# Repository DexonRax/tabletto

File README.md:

# Tabletto V1S

> A ridiculously fast DIY osu! "tablet" built around a **SCARA arm** mechanism, powered by an **RP2040** (RP2040-Zero) and **dual AS5600 magnetic rotary encoders**.

Tabletto V1S was designed with one goal in mind: **the lowest possible input latency** using inexpensive, easy-to-source components, fully 3D printed mechanics, and custom open-source PCBs.

---

# Gallery

---

# Features

* ⚡ **1000 Hz report rate** (1 ms USB HID polling)
* 🎯 Minimal cursor jitter
* 🚀 Faster than most commercial graphics tablets
* 🖨️ Fully 3D printable mechanical design
* 🔩 Custom open-source **KiCad PCBs** (base + arm sensor board)
* 🧠 On-device forward kinematics — standalone, works with **OpenTabletDriver**
* 🔘 Physical button: **short press** toggles the tablet, **hold 3 s** to calibrate
* 💾 Calibration stored in the RP2040's flash, survives power cycles

---

# How it works

Tabletto uses a **SCARA (Selective Compliance Assembly Robot Arm)** mechanism.

Two **AS5600 magnetic rotary encoders** measure the angle of each arm joint — one lives on the base PCB, the other on a small board at the elbow. The RP2040 firmware reads both encoders over two separate I2C buses and computes the pen position with forward kinematics, then sends it to the host as a vendor-defined HID report.

Because the sensors provide high-resolution angle measurements and the mechanism has very little moving mass, the result is an extremely responsive pointing device well suited for rhythm games like osu!.

---

# Hardware

Required components:

| Quantity | Part                            |
| -------- | ------------------------------- |
| 1        | RP2040-Zero (or similar module) |
| 2        | AS5600 Magnetic Rotary Encoder  |
| 2        | MR128ZZ 8x12x3.5mm Bearings     |
| 4        | 4.7kΩ Resistor                  |
| 1        | 100nF Capacitor                 |
| 1        | JST XH 2.54mm straight connector|
| 1        | JST XH 2.54mm male cable        |
| 1        | Keyboard Switch                 |
| 4        | 10mm M3 Screws                  |
| 2        | 4x3mm Diametral magnets         |
| —        | 3D Printed Parts                |
| —        | PCBs - from `V1S/pcb`           |

Both boards have **3.2 mm M3 mounting holes**.

---

# PCBs

The electronic design is open source and lives in [V1S/pcb](V1S/pcb):

* **`pcb/base`** — base board: RP2040-Zero module, one AS5600, 4.7kΩ I2C pull-ups, calibration button, and a 4-pin connector to the arm board.
* **`pcb/arm`** — elbow board: the second AS5600 with a 100 nF decoupling cap, connected over a short 4-pin cable.

Open the `.kicad_sch` / `.kicad_pcb` files in KiCad 8+ and order them from any PCB fab (both boards are two-layer).

## Firmware pin mapping

| Function        | Pin  |
| --------------- | ---- |
| I2C0 SDA (base) | GP0  |
| I2C0 SCL (base) | GP1  |
| I2C1 SDA (arm)  | GP2  |
| I2C1 SCL (arm)  | GP3  |
| Calibration btn | GP4  |

---

# Firmware

Located in [V1S/firmware](V1S/firmware). Built with the **Raspberry Pi Pico SDK** and **TinyUSB**.

## Flashing (easiest)

A precompiled build is included at `V1S/firmware/precompiled/tabletto.uf2`:

1. Plug the RP2040-Zero into USB while holding **BOOT**
2. Drag and drop `tabletto.uf2` onto the USB drive that appears
3. Done — the device enumerates as a HID tablet (VID `0x1209`, PID `0x0001`)

## Building from source

Requires the Pico SDK and CMake:

```
cd V1S/firmware
cmake -B build -DPICO_SDK_PATH=/path/to/pico-sdk
make -C build
```

The resulting `build/tabletto.uf2` can be flashed as above.

---

# Driver

Tabletto exposes a standard vendor-defined HID report, so **no custom driver is needed** — just use [OpenTabletDriver](https://github.com/OpenTabletDriver/OpenTabletDriver).

Import the configuration from `V1S/driver/OpenTabletDriver Configuration/TablettoV1S.json` 
into OpenTabletDriver (restart needed): 
- Linux: ~/.local/share/OpenTabletDriver/Configurations/ (create it if missing: mkdir -p ~/.local/share/OpenTabletDriver/Configurations)
- Windows: %LOCALAPPDATA%\OpenTabletDriver\Configurations

It defines:
* Work area: **180 × 112.5 mm** (X 0–18000, Y 0–11250, 0.01 mm units)
* Input report length: 9 bytes
* `libinputoverride: 1` for reliable Linux behavior

---

# Calibration

1. With the tablet connected, **pull the arm straight down** (toward you), so both sensors read their reference position.
2. **Hold the button for 3 seconds.**
3. Short-press the button at any time to toggle the tablet on/off.

Direction tuning lives in the firmware (`X_DIR` / `Y_DIR` in `main.c`) if the axes ever need flipping.

---

# Why SCARA?

Unlike traditional graphics tablets, Tabletto directly measures arm angles with magnetic encoders.

Advantages include:

* extremely low latency
* high update rate
* no pressure to use specialized tablet hardware
* inexpensive components
* entirely repairable and printable

---

# 3D Printing

All `.stl` files can be found in [V1S/models](V1S/models):

| File                  | Purpose                           |
| --------------------- | --------------------------------- |
| `arm1_up.stl`         | Arm segment 1 (magnet-up variant) |
| `arm1_down.stl`       | Arm segment 1 (magnet-down variant) |
| `arm2.stl`            | Arm segment 2 (elbow to pen)      |
| `base_down_workarea.stl` | Bottom side of the base |
| `base_up_debug.stl`   | Upper side of the base (debug has a cutout for RP2040 buttons) |
| `workarea.stl`        | Flat work area plate              |
| `offset_nib_3.6mm.stl` | Nut-like offset for spacing (6 needed)    |

Every structural component is designed to be **3D printed** — no CNC machining or laser cutting required. Place the magnets that came with the AS5600s on top of the bearings.

---

# Repository layout

```
V1S/
├── driver/    OpenTabletDriver configuration (JSON)
├── firmware/  RP2040 firmware (Pico SDK + TinyUSB) + precompiled UF2
├── models/    3D printable STL files
└── pcb/       KiCad sources: base board + arm sensor board
```

---

# License

Copyright (C) 2026 Dexon Rax

Tabletto is free and open source (AGPLv3) for personal and noncommercial
use — this covers the RP2040 firmware, the OpenTabletDriver configuration,
the 3D printable models, and the KiCad PCB sources.

💡 Want to manufacture or sell Tabletto commercially, or use it in a
closed product? Contact me for licensing — see LICENSE-COMMERCIAL.md.

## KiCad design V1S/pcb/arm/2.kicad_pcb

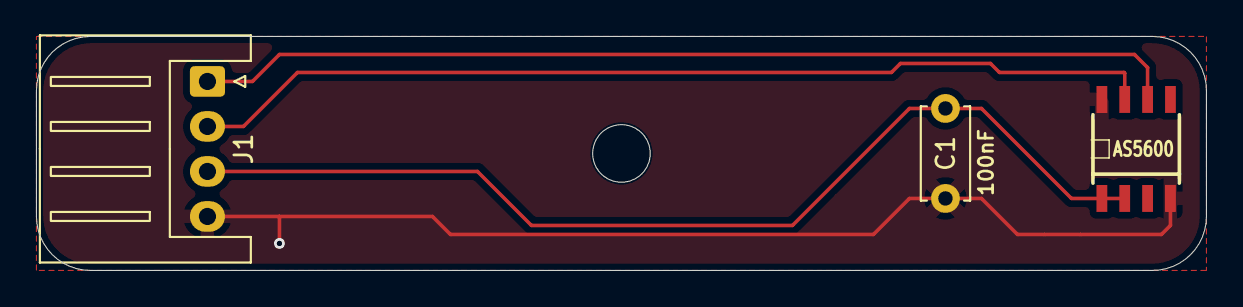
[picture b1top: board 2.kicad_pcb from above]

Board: 2 copper layers, 65.0 x 13.0 mm, 3 parts (0 on the bottom side), 4 nets.

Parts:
AS5600: AS5600; SOIC8
C1: 100nF; C_Disc_D5.0mm_W2.5mm_P5.00mm
J1: Conn_01x04_Pin; JST_XH_S4B-XH-A_1x04_P2.50mm_Horizontal

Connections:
unnamed: AS5600.6 (SDA), J1.1
unnamed: AS5600.7 (SCL), J1.2
unnamed: AS5600.1 (VDD5V), AS5600.2 (VDD3V3), C1.1, J1.3
unnamed: AS5600.4 (GND), AS5600.8 (DIR), C1.2, J1.4

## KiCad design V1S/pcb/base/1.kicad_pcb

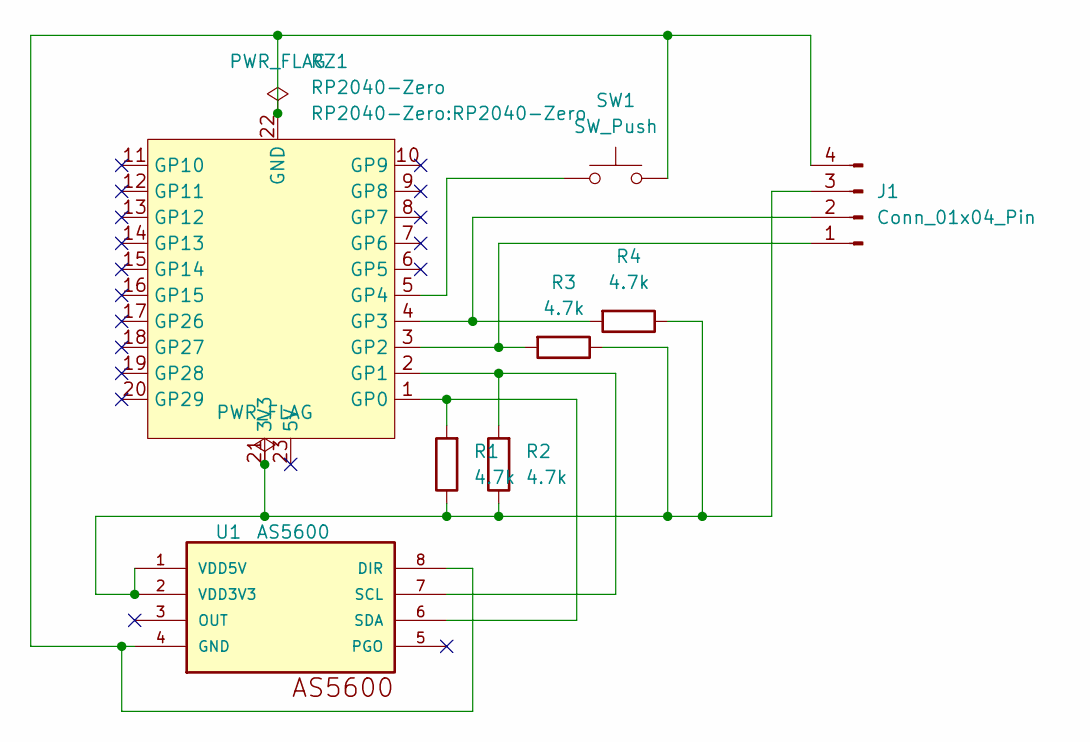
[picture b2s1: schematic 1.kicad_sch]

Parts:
J1: Conn_01x04_Pin; JST_XH_B4B-XH-A_1x04_P2.50mm_Vertical
R1, R2, R3, R4: 4.7k; R_Axial_DIN0207_L6.3mm_D2.5mm_P7.62mm_Horizontal
RZ1: RP2040-Zero
SW1: SW_Push; SW_Cherry_MX_1.00u_PCB
U1: AS5600; SOIC8

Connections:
unnamed: J1.1, R3.2, RZ1.3 (GP2)
unnamed: J1.2, R4.2, RZ1.4 (GP3)
unnamed: J1.3, R1.1, R2.1, R3.1, R4.1, RZ1.21 (3V3), U1.1 (VDD5V), U1.2 (VDD3V3)
unnamed: J1.4, RZ1.22 (GND), SW1.2, U1.4 (GND), U1.8 (DIR)
unnamed: R1.2, RZ1.1 (GP0), U1.6 (SDA)
unnamed: R2.2, RZ1.2 (GP1), U1.7 (SCL)
unnamed: RZ1.5 (GP4), SW1.1

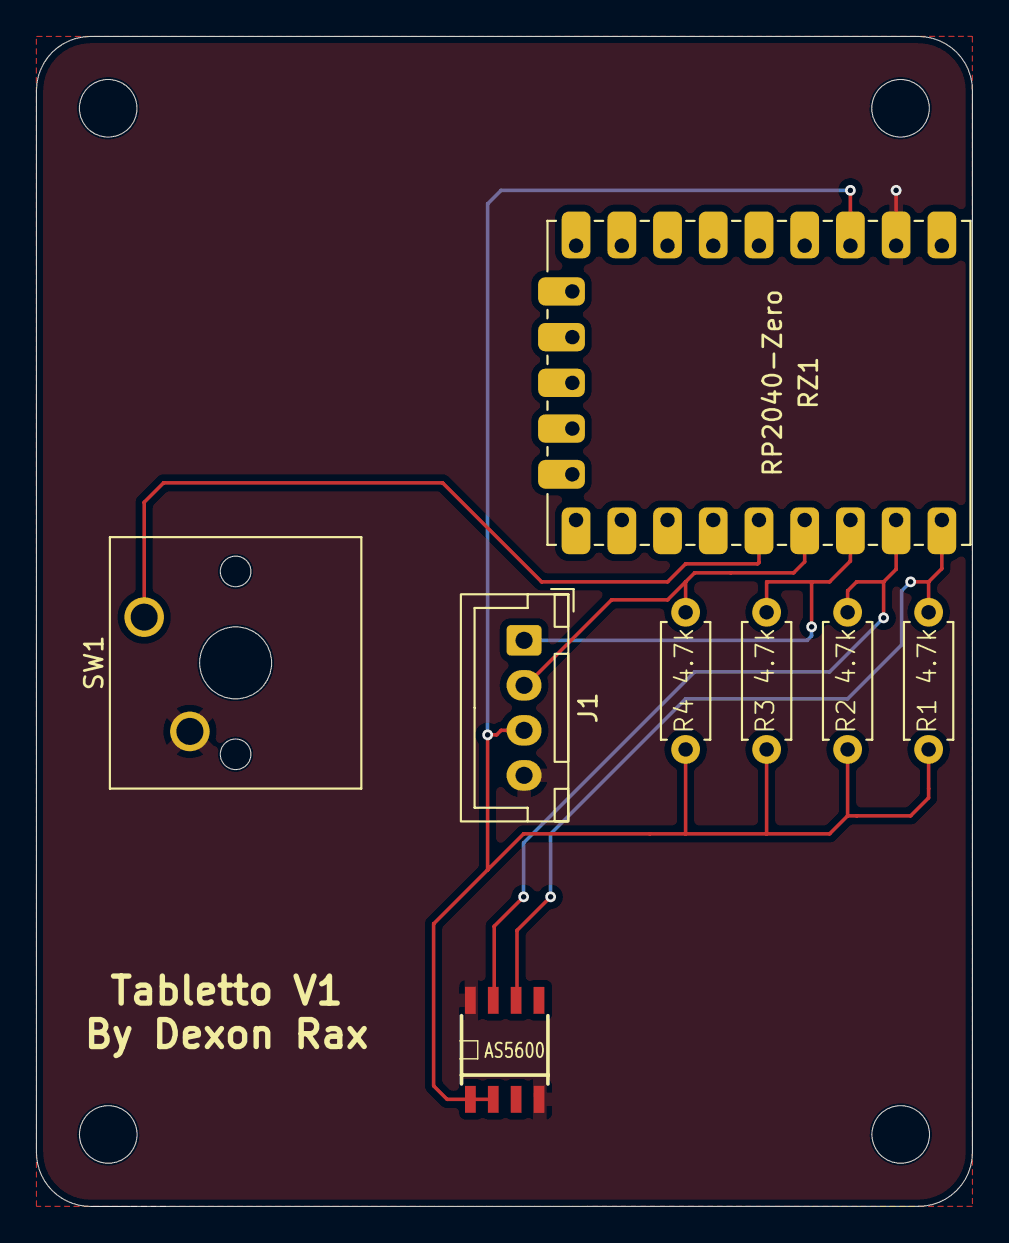
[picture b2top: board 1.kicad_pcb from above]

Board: 2 copper layers, 52.0 x 65.0 mm, 8 parts (0 on the bottom side), 7 nets.
